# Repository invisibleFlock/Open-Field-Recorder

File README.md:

Welcome to the project page for the OFR

# What is OFR:

OFR is the Open Field Recorder created by Invisible Flock (and friends). 

With support and in collaboration with Bournemouth University and Professor Amanda H Korstjens from [LEAP](https://go-leap.wixsite.com/home/amanda-korstjens).

It is an open hardware and software platform for remote long form bio-acoustic recording. 

It is created for *sound artists, conservationists, scientist* and anyone who wants or needs to record audio and environmental data for long periods of time in inhospitable environments. 

It is modular, hackable, meshable and useful in a wide series of situations and applications.

# Why does it exit:

The OFR was created by Invisible Flock to solve a specific need we had whilst recording large sections of a rainforest in Sumatra. 

We needed recorders that would function in the difficult conditions of the forest for long periods of time in order to monitor the biodiversity of the area and that we could sync together to create large scale multichannel sound installations with audio quality as close to our main field recorders as possible.

The OFR for us was an attempt to bridge a gap that was not currently being fulfilled by other products on the market allowing us to record stereo audio from high quality microphones that were synced via GPS. 

Whilst there are other excellent products that already exist for bio-acoustic monitoring, most notably the [audio-moth](https://www.openacousticdevices.info/), the [solo](https://solo-system.github.io/home.html), and the [swift](https://www.birds.cornell.edu/ccb/wp-content/uploads/2016/09/SWIFT-SD-Card-Formatting-Protocol.pdf) none provided us with the specifics we wanted for this project but you may find they are good fit for you depending on your aims.

# What's inside it:

Expand ability and flexibility were important for us in this design and was the ability for other users to build on it and hack the recorder into their own needs. Version 1.1 is built on the [Spresense](https://developer.sony.com/develop/spresense/) a multicore development board platform by Sony which is programmable via the Arduino IDE.

# So what can i do with it:

You can record the sound of landscapes in near studio quality for long periods of time day and night in all weather conditions and use GPS and analogue sensors to sync multiple recorders and data readings over time and space.

# Give me some specs:

Version 1.1 of the OFR:

- 2 to 4 channel audio
- 48khz to 198khz audio quality
- time and location sync via GPS to enable meshing of multiple recorders
- sensor logging to sync analogue sensor data points to audio files
- options for multiple budgets and microphone quality (ranging from cheap electrec mics to DPA 4060)
- phantom power 
- theoretical running time of 7 days (dependent on specs used and batteries employed)
- custom shield for extra robustness and direct tangible access to key parameters
- design for inhospitable terrain able to withstand tropical rain storms and sub zero temps

# What are you offering on here:

We do not currently sell the OFR as this would be neither cost effective for us or for you and neither would it be practical for us as we are a small studio whose main output is not product manufacture. 

Instead through this site we are working towards offering the full spec and design files for the OFR, including the CAD files for the box interior, the schematics for the shield, the codebase for creating and running your own version, a software interface for controlling and setting up your recorders and a willingness to engage and share knowledge with you in whatever project you embark on with the OFR.  

This is all provided free (as in both beer and speech) but would appreciate a mention or shoutout as we are hoping to build a community around the creative use of the OFR.

# How do i use it:

Right now getting a build of your own up and running would require a bit of work on your part but we are here to help with that. In the first instance you will need to head over the [hardware](hardware/hardwareReadme.md) page which lists and explains the next steps. We are working to make the time and effort needed to get you up and running with the OFR system as easy as possible so you can get out in the field with it.

The project and the code is available on the github although at the time of writing we cannot be certain that it is a working version - over the next month we will get all of this documentation up to scratch and ready to flash onto your own OFR system.

# What are the future plans:

Future versions of the OFR will hopefully offer other platforms to run the OFR on as well as provide longer recording time and more i/o options. 

We are currently developing the shield (pictured above) which will increase the OFR's robustness in the field as well as providing physical tangible control over some key parameters of the recorder. We are developing this with our friends at [Digital Nativ](https://www.instagram.com/digitalnativ/) based in Jakarta. We hope that we will be able to offer the shields to  purchase in mid/late 2020. 

We are also working closely with our friend and long time collaborator Romit Raj from design agency [Quicksand](http://quicksand.co.in/) who is working to develop a new ML based detection and bio-auditing system and we hope to be able to release a build of the OFR fine tuned to interface and provide the best possible results with his system. 

# Where is it being used at moment:

The OFR has been deployed in Sumatra in 2019 and will  return there in mid 2020 to help monitor and establish an elephant migration corridor. It is being used in the sate of Karnataka in India where it is similarly being used on farms where human elephant conflict is a recurring issue. Later in 2020 it will be deployed across the North of Finland to record the sound of the yearly freeze as part of an ongoing project with the Sub Zero collective of artists and scientists working on the edge of the artic. Hopefully we can keep this list updated and growing.

# Can i hear what it sounds like:

Yes:
[A loud monkey cackle](/soundSample/cackle-veryloud-box1.wav).
[a storm](/soundSample/THUNDERSTORM-CLIP-BOX8.wav).
[and an orangutan](/soundSample/O-TANG-CLIP.wav).

All of these were recorded in Sumatra in 2019.

# Who else is part of this project:

The OFR was first designed and created as part of a collaboration between Invisible Flock and research undertaken by academics from [LEAP](https://go-leap.wixsite.com/home) specifically Amanda H Korstjens and Helen Slater and their ongoing research through Bournemouth University in the Leuser Ecosystem.

If you have any questions about the OFR, using it, deploying it or anything generally please do not hesitate to get in touch.

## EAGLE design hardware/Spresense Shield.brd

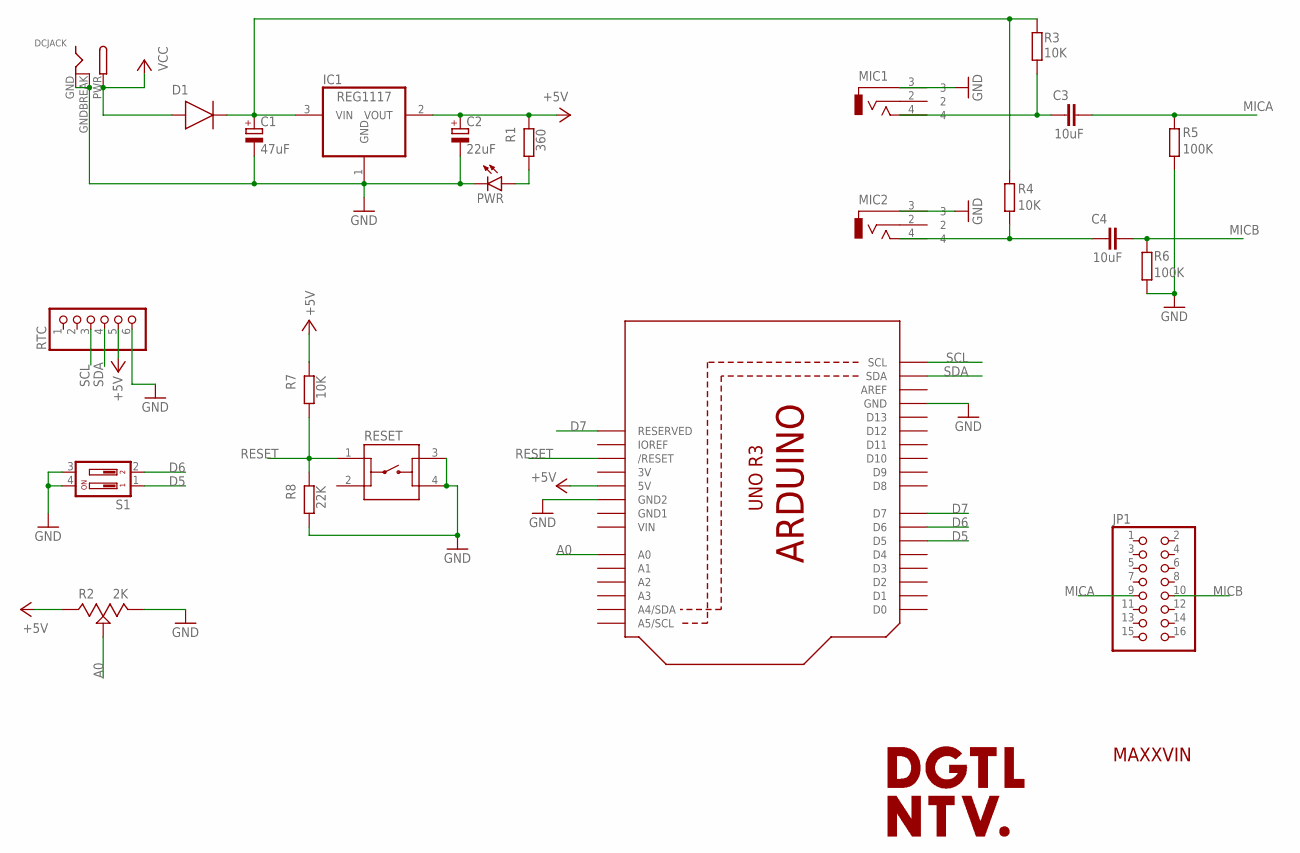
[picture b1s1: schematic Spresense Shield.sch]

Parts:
C1: 47uF; 153CLV-0605
C2: 22uF; 153CLV-0605
C3, C4: 10uF; CAPC2012X110
D1: DIODEDO-214AC(SMA); DIOM5226X290N
DCJACK: DCBARRELPTH; DCJACK_2MM_PTH
IC1: REG1117; SOT223
JP1: PINHD-2X8; 2X08
MIC1, MIC2: PJ-320F
PWR: LEDCHIP-LED0805; CHIP-LED0805
R1: 360; RESC2012X65
R2: 2K; 3362P-1-103LF
R3, R4, R7: 10K; RESC2012X65
R5, R6: 100K; RESC2012X65
R8: 22K; RESC2012X65
RESET: 1825910-6
RTC: PINHD-1X6; 1X06
S1: DS02; DS-02
U1: ARDUINOR3-DIMENSION; ARDUINOR3

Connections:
3V: U1.3V
+5V: C2.+, IC1.2 (VOUT), R1.1, R2.3, R7.1, RTC.5, U1.5V
A0: R2.2, U1.A0
D5: S1.1, U1.D5
D6: S1.2, U1.D6
D7: U1.D7, U1.RESERVED
GND: C1.-, C2.-, DCJACK.GND, DCJACK.GNDBREAK, IC1.1 (GND), MIC1.3, MIC2.3, PWR.C, R2.1, R5.2, R6.2, R8.2, RESET.3, RESET.4, RTC.6, S1.3, S1.4, U1.GND, U1.GND2
GND1: U1.GND1
MICA: C3.2, JP1.9, R5.1
MICB: C4.2, JP1.10, R6.1
unnamed: C4.1, MIC2.4, R4.2
unnamed: C1.+, D1.2 (C), IC1.3 (VIN), R3.1, R4.1
unnamed: C3.1, MIC1.4, R3.2
unnamed: PWR.A, R1.2
RESET: R7.2, R8.1, RESET.1, U1.RESET (/RESET)
SCL: RTC.3, U1.SCL
SDA: RTC.4, U1.SDA
VCC: D1.1 (A), DCJACK.PWR
VIN: U1.VIN

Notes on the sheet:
MAXXVIN

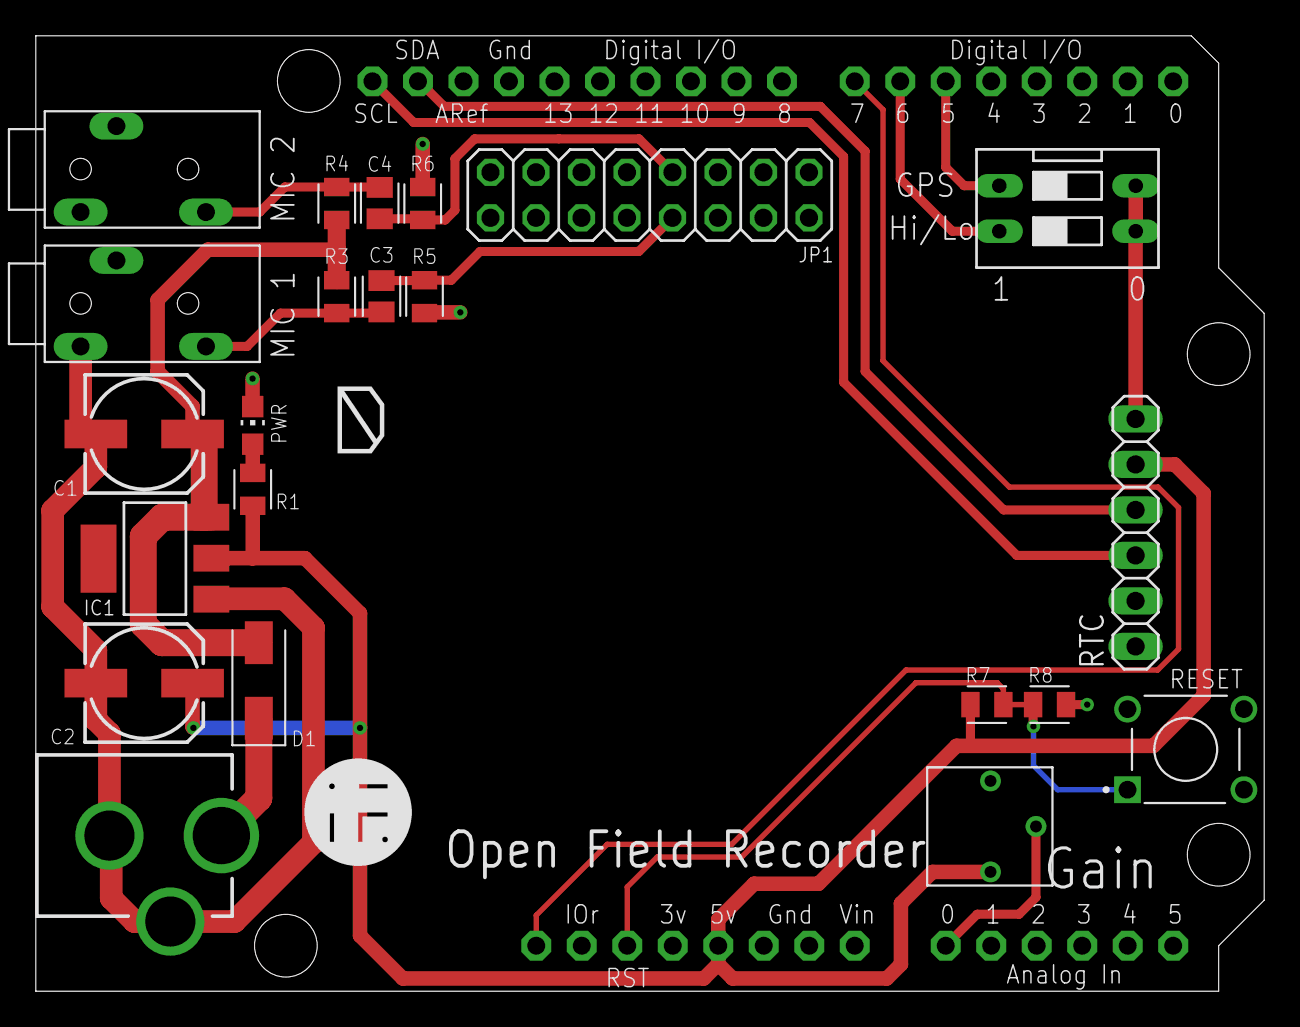
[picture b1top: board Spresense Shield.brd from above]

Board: 2 copper layers, 68.6 x 53.3 mm, 25 parts (0 on the bottom side), 16 nets.

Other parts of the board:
U$1: IF_SOLID_LOGO_TOP_6MM
U$4: D_LOGO_TOP_2.7MM

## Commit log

2020-02-28 Add files via upload
    the code for the core and the subcore as it stands now - some of the core variables have been exposed but need hooking into their relative conditional states - small chance the OFR main code might no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
2020-02-28 Add files via upload
    pdf of instructions and the 'Original' sletch which is the last working version before we started to build it out
2020-03-20 Set theme jekyll-theme-midnight
2020-03-20 Add files via upload
    circuit diagram for shield
2020-03-20 Update README.md
    added hardware link
2020-03-20 Create images
